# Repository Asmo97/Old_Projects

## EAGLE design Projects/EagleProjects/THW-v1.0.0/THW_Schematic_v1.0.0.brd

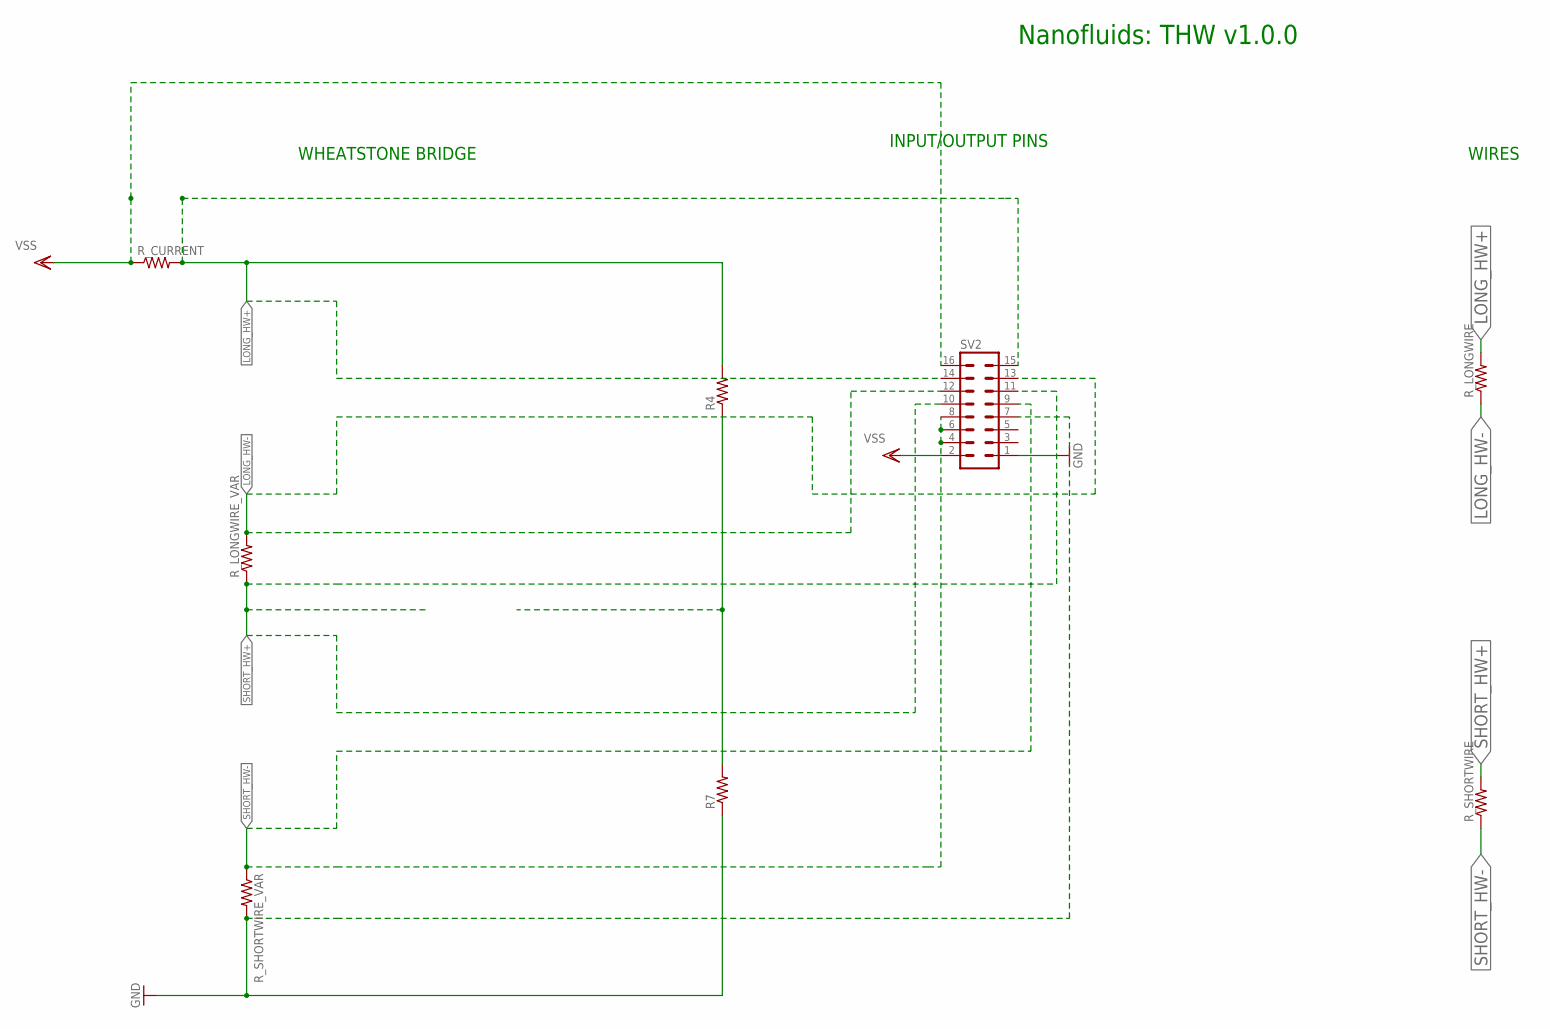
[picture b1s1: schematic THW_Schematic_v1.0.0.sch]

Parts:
R4, R7: R-US_M0805; M0805
R_CURRENT: R-US_M0805; M0805
R_LONGWIRE: R-US_M0805; M0805
R_LONGWIRE_VAR: R-US_M0805; M0805
R_SHORTWIRE: R-US_M0805; M0805
R_SHORTWIRE_VAR: R-US_M0805; M0805
SV2: MA08-2W

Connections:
GND: R7.1, R_SHORTWIRE_VAR.2, SV2.1, SV2.7
LONG_HW+: R4.2, R_CURRENT.2, R_LONGWIRE.2, SV2.14, SV2.15
LONG_HW-: R_LONGWIRE.1, R_LONGWIRE_VAR.2, SV2.12, SV2.13
unnamed: R4.1, R7.2
SENS_1+: R_CURRENT.1, SV2.16
SHORT_HW+: R_LONGWIRE_VAR.1, R_SHORTWIRE.2, SV2.10, SV2.11
SHORT_HW-: R_SHORTWIRE.1, R_SHORTWIRE_VAR.1, SV2.4, SV2.6, SV2.8, SV2.9
VSS: SV2.2

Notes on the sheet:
Nanofluids: THW v1.0.0
WHEATSTONE BRIDGE
WIRES
INPUT/OUTPUT PINS

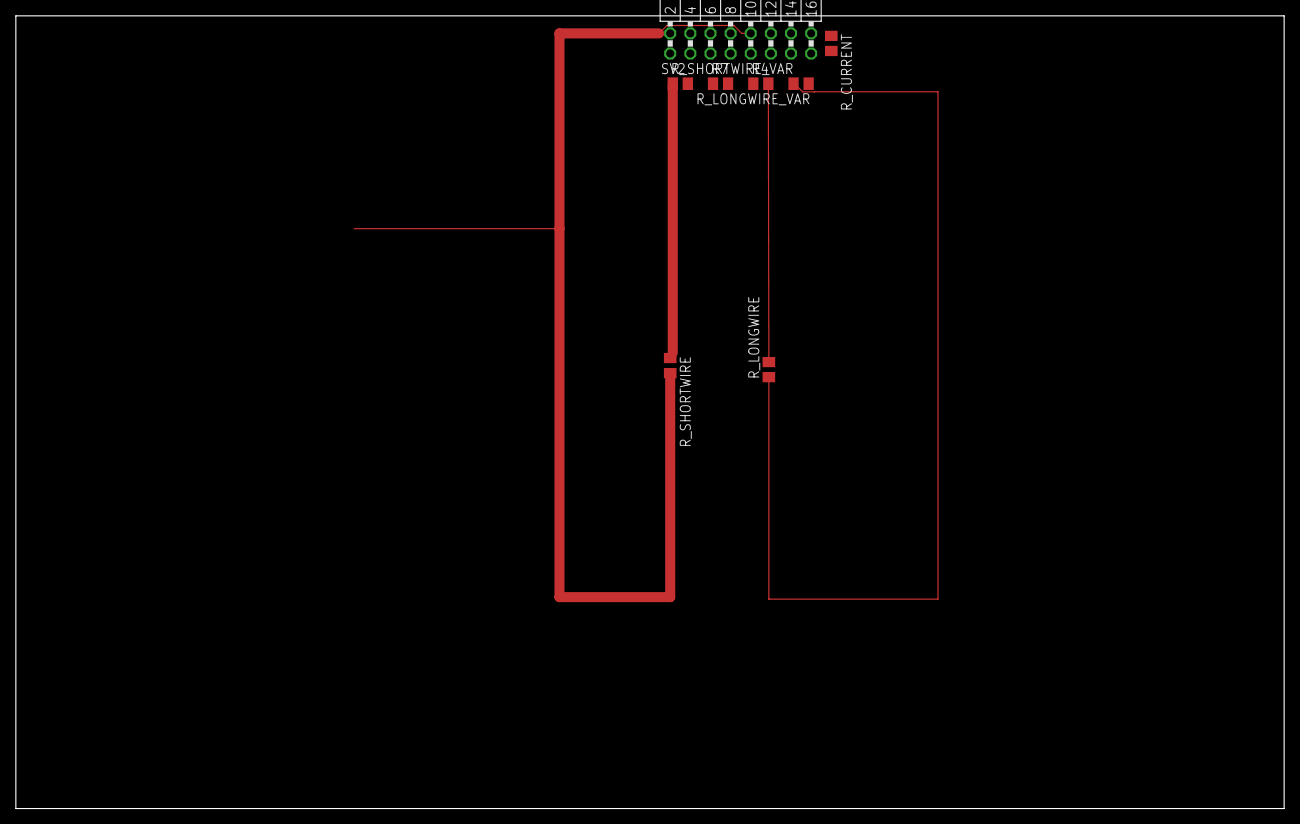
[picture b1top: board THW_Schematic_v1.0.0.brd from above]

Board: 2 copper layers, 160.0 x 100.0 mm, 8 parts (0 on the bottom side), 7 nets.

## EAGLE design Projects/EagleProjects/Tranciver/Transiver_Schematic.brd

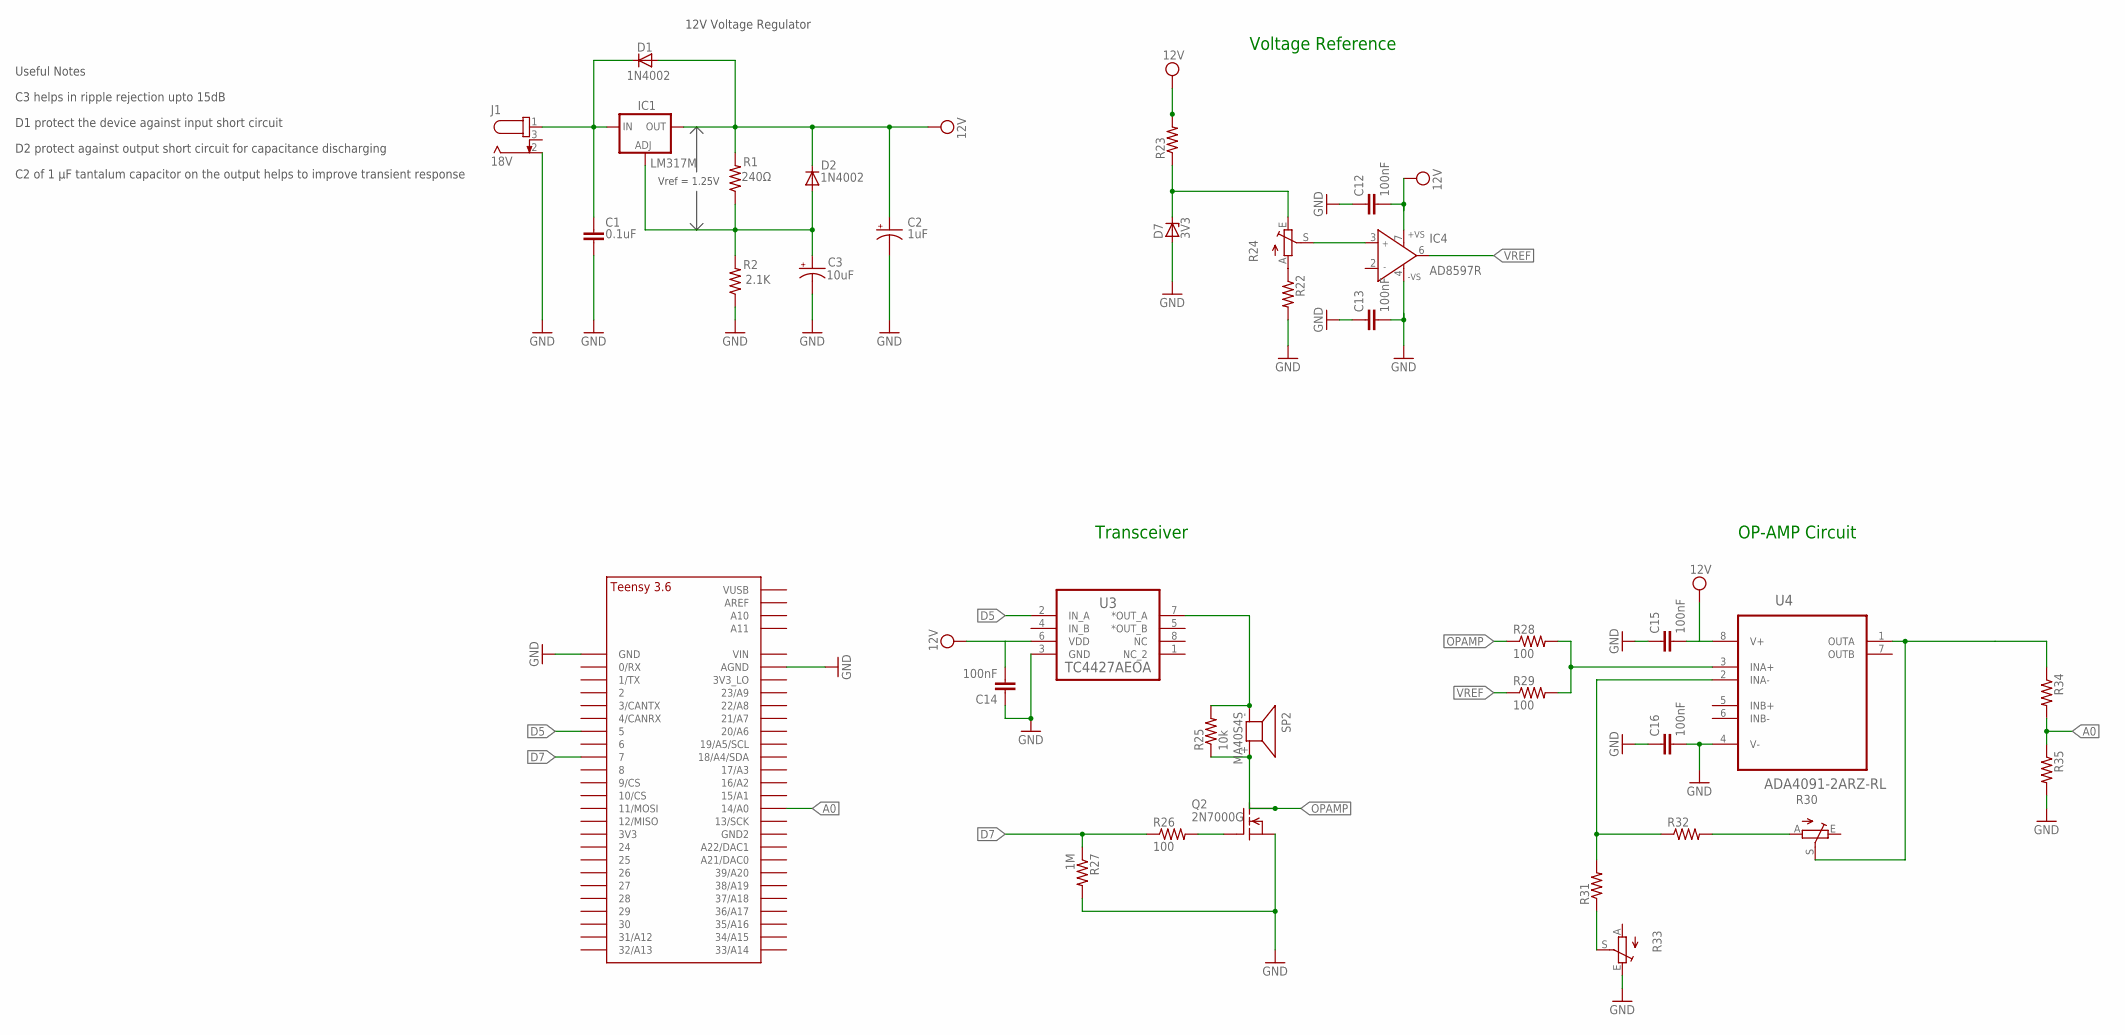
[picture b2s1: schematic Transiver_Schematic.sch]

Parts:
C1: 0.1uF; C075-052X106
C2: 1uF; 085CS_1AR
C3: 10uF; 085CS_1AR
C12, C13, C14, C15, C16: 100nF; C2.5-3
D1, D2: 1N4002; DO41-10
D7: 3V3; DO41Z10
IC1: LM317MBSTT3; SOT223; PARTNUMBER LM317M
IC4: AD8597R; SO8
J1: 18V; 69410X303002
Q2: 2N7000G; TO92-INLINE
R1: 240Ω; M0805
R2: 2.1K; M0805
R22, R23, R31, R32, R34, R35: R-US_M0805; M0805
R24, R30, R33: TRIM_EU-CA6V; CA6V
R25: 10k; R0805
R26, R28, R29: 100; M0805
R27: 1M; M0805
SP2: MA40S4S; MA40
U3: TC4427AEOA; SOIC127P600X175-8N
U4: ADA4091-2ARZ-RL; SOIC127P600X175-8N
U$1: TEENSY_3.5/3.6_BASIC

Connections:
12V: C12.2, C15.2, IC4.7 (+VS), U4.8 (V+)
18V: C1.1, D1.C, IC1.3 (IN), J1.1
A0: R34.2, R35.1, U$1.14/A0
D5: U3.2 (IN_A), U$1.5
D7: R26.1, R27.1, U$1.7
GND: C1.2, C2.-, C3.-, C12.1, C13.1, C13.2, C14.1, C15.1, C16.1, C16.2, D7.A, IC4.4 (-VS), J1.2, R2.1, R22.2, R33.E, R35.2, U3.3 (GND), U4.4 (V-), U$1.AGND, U$1.GND
unnamed: C3.+, D2.A, IC1.1 (ADJ), R1.1, R2.2
unnamed: IC4.3 (IN+), R24.S
unnamed: D7.C, R23.1, R24.E
unnamed: R22.1, R24.A
unnamed: R28.2, R29.2, U4.3 (INA+)
unnamed: C14.2, U3.6 (VDD)
unnamed: R25.2, SP2.- (1), U3.7 (*OUT_A)
unnamed: Q2.2 (GATE), R26.2
unnamed: R31.2, R32.1, U4.2 (INA-)
unnamed: R30.S, R34.1, U4.1 (OUTA)
unnamed: R31.1, R33.S
unnamed: R30.A, R32.2
OPAMP: Q2.1 (SRC), Q2.3 (DRN), R25.1, R27.2, R28.1, SP2.+ (2)
VDD: C2.+, D1.A, D2.C, IC1.4 (OUT), R1.2, R23.2
VREF: IC4.6 (OUT), R29.1

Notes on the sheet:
12V Voltage Regulator
C3 helps in ripple rejection upto 15dB
D1 protect the device against input short circuit
D2 protect against output short circuit for capacitance discharging
C2 of 1 µF tantalum capacitor on the output helps to improve transient response
Useful Notes
Vref = 1.25V
Transceiver
OP-AMP Circuit
Voltage Reference

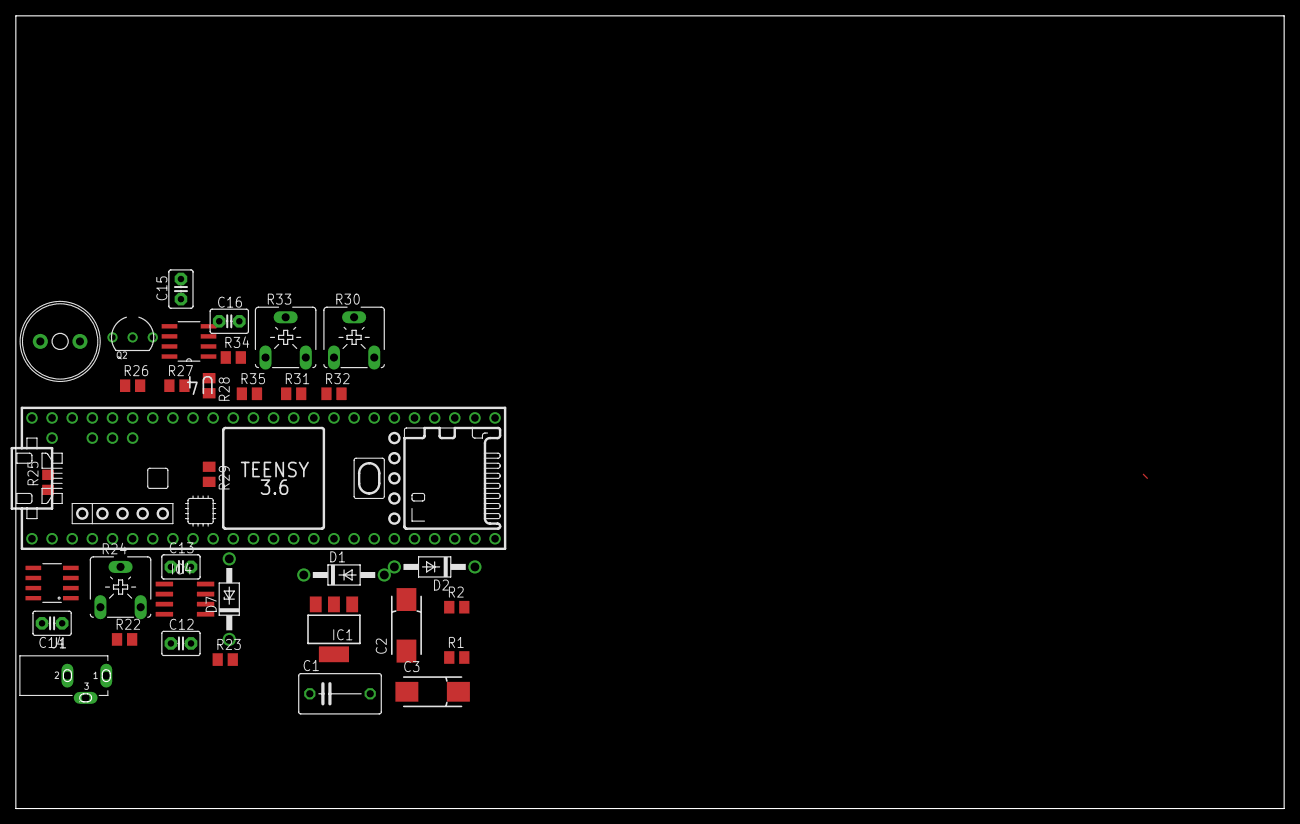
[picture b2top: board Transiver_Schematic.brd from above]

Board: 4 copper layers, 160.0 x 100.0 mm, 35 parts (0 on the bottom side), 21 nets.

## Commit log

2018-06-08 adding arduino code
2018-06-08 Adding the OLED Pong game
2018-06-08 added images for different scenes
2018-06-08 Text file for usefull links
2018-06-12 playin around with RBG LED, and serial communcation
2018-07-02 Added Ball Simulation 1
2018-07-02 deleted some unwanted files
2018-07-02 added some comments
2018-07-03 added a link
2018-07-09 Rewriting ballsim code
2018-07-09 Re-writing BallSimulation
2018-07-09 Re-Writted the ball_simulation1 code
2018-07-11 Added Particle Simulation with standard euler method
2018-07-11 Type data to .csv file (rewrite later)
2018-07-12 :O Even better code to write data to file! -- Work on matplotlib next
2018-07-12 better code for writing data files - working on python script
2018-07-13 Re-Organising files
2018-07-13 working on matplotlib
2018-07-16 learn oop python, then do matplotlib
2018-07-16 print this at uni
2018-07-17 practicing python oop
2018-07-18 understanding matplotlib library
2018-07-20 LEDs for spectrometer
2018-07-26 created seperate files for particleData
2018-07-26 paraview simulation file saved file
2018-07-28 planetary orbit simulation
2018-07-28 included paraview for orbit simulation
2018-07-28 python visuals
2018-07-30 more work on euler
2018-07-30 euler energy testing
2018-07-31 Fixed lol
2018-07-31 working on solar system.. a bit past my bed time tho
2018-07-31 Working on solar system plotting in python
2018-08-01 I think the maths for planets is wrong here?
2018-08-02 closer planets dont orbit!
2018-08-16 changed data for attributes of planets
2018-09-03 Transceiver test code
2018-09-03 fixed
2018-09-04 Burst mode added
2018-09-04 burst mode
2018-09-08 timer interrupts
2018-09-08 interrupet timer
2018-09-13 eagle
2018-09-16 schmatic for eagle
2018-09-18 eagle work
2018-09-25 THW eagle
